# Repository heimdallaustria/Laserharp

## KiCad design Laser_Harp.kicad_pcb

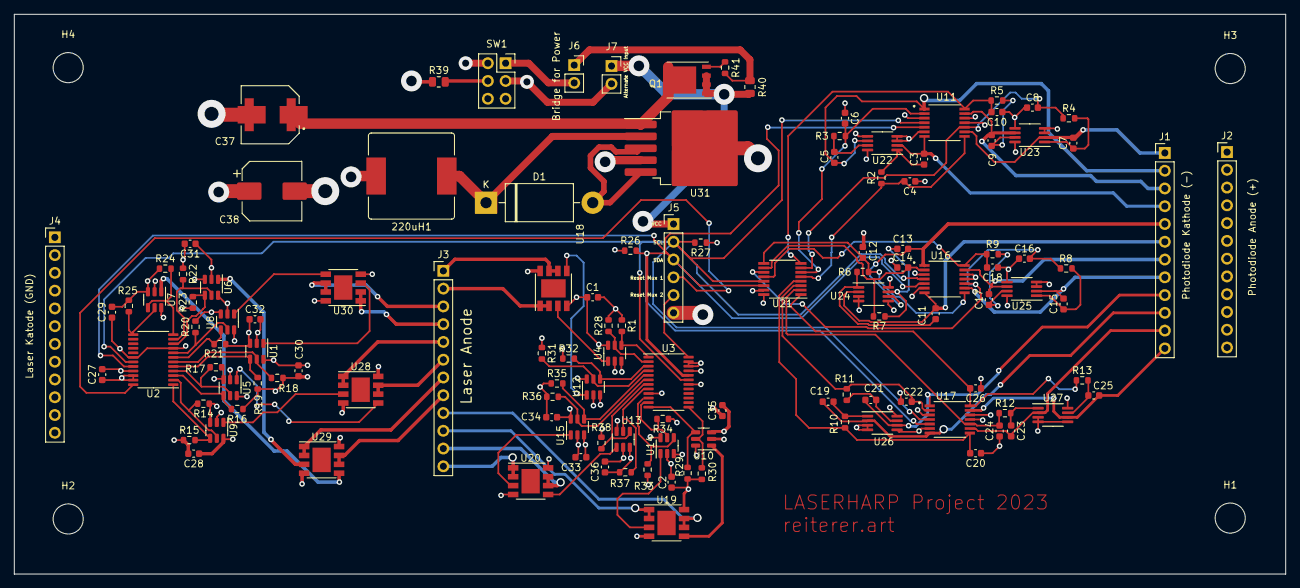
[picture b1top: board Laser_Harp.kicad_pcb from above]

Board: 4 copper layers, 181.7 x 80.0 mm, 125 parts (0 on the bottom side), 97 nets.

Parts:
220uH1: L; L_Bourns_SRR1210A
C1, C2, C27, C28, C29, C30, C31, C32, C33, C34, C35, C36: 0.1uF; C_0603_1608Metric
C3, C5, C7, C9, C11, C13, C15, C17, C19, C21, C23, C25: 22pF; C_0603_1608Metric
C4, C6, C8, C10, C12, C14, C16, C18, C20, C22, C24, C26: 1nF; C_0603_1608Metric
C37: 470uF; CAP_EEEFT1E471AV
C38: 470uF; CP_Elec_8x10
D1: 1N5822; D_DO-201AD_P15.24mm_Horizontal
H1, H2, H3, H4: MountingHole; MountingHole_4.3mm_M4_DIN965
J1, J2, J3, J4: Conn_01x12_Socket; PinHeader_1x12_P2.54mm_Vertical
J5: Conn_01x06_Socket; PinHeader_1x06_P2.54mm_Vertical
J6, J7: Conn_01x02_Pin; PinSocket_1x02_P2.54mm_Vertical
Q1: SQJ147ELP-T1; PowerPAK_SO-8_Single
R1, R14, R15, R16, R17, R18, R19, R20, R21, R22, R23, R24, R25, R26, R27, R28, R29, R30, R31, R33, R34, R35, R36, R37, R38: 10K; R_0603_1608Metric
R2, R3, R4, R5, R6, R7, R8, R9, R10, R11, R12, R13: 100; R_0603_1608Metric
R32: R_Small; R_0603_1608Metric
R39: 130; R_0805_2012Metric
R40: 10K; R_0805_2012Metric
R41: 30; R_0603_1608Metric
SW1: G12JPF; PinSocket_2x03_P2.54mm_Vertical_editpin
U1, U4, U5, U6, U7, U8, U9, U10, U12, U13, U14, U15: MCP4725; SOT-23-6
U2, U3: TCA9548AMRGER; TSSOP-24_4.4x7.8mm_P0.65mm
U11, U16, U17: MCP4432; SOP65P640X120-14N
U18, U19, U20, U28, U29, U30: TS912AIDT; Diodes_SO-8EP
U21: MAX11617; QSOP-16_3.9x4.9mm_P0.635mm
U22, U23, U24, U25, U26, U27: OPA2381AIDGKT; MSOP-8_3x3mm_P0.65mm
U31: LM2576HVS-3.3; TO-263-5_TabPin3

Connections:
3.3V: 220uH1.2, C1.2, C2.2, C27.2, C28.2, C29.2, C30.1, C31.2, C32.1, C33.2, C34.1, C35.2, C36.1, C38.1, R1.1, R14.1, R15.1, R16.1, R17.1, R18.1, R19.1, R20.2, R21.2, R22.1, R23.1, R24.1, R25.2, R26.1, R27.1, R28.1, R29.1, R30.2, R31.1, R32.1, R33.1, R34.1, R35.1, R36.1, R37.2, R38.2, R39.1, U1.3 (VDD), U2.21 (VCC), U3.18 (A2), U3.21 (VCC), U4.3 (VDD), U5.3 (VDD), U6.3 (VDD), U7.3 (VDD), U8.3 (VDD), U9.3 (VDD), U10.3 (VDD), U11.12 (VCC), U12.3 (VDD), U13.3 (VDD), U14.3 (VDD), U15.3 (VDD), U16.11 (A1), U16.12 (VCC), U17.3 (A0), U17.12 (VCC), U18.8 (VCC_2), U19.8 (VCC_2), U20.8 (VCC_2), U21.16 (Vdd), U22.8 (V+), U23.8 (V+), U24.8 (V+), U25.8 (V+), U26.8 (V+), U27.8 (V+), U28.8 (VCC_2), U29.8 (VCC_2), U30.8 (VCC_2), U31.4 (FB)
+12V: J5.1, J7.1, Q1.1 (Source), Q1.2 (Source), Q1.3 (Source), R40.1
ADC_IN0: C4.2, R2.1, U11.8 (P1W), U21.5 (AIN0)
ADC_IN1: C6.2, R3.1, U11.2 (P3B), U21.6 (AIN1)
ADC_IN2: C8.2, R4.1, U11.10 (P0B), U21.7 (AIN2)
ADC_IN3: C10.2, R5.1, U11.14 (P2W), U21.8 (AIN3)
ADC_IN4: C12.2, R6.1, U16.8 (P1W), U21.9 (AIN4)
ADC_IN5: C14.2, R7.1, U16.2 (P3B), U21.10 (AIN5)
ADC_IN6: C16.2, R8.1, U16.10 (P0B), U21.11 (AIN6)
ADC_IN7: C18.2, R9.1, U16.14 (P2W), U21.12 (AIN7)
ADC_IN8: C20.2, R10.1, U17.8 (P1W), U21.4 (AIN8)
ADC_IN9: C22.2, R11.1, U17.2 (P3B), U21.3 (AIN9)
ADC_IN10: C24.2, R12.1, U17.10 (P0B), U21.2 (AIN10)
ADC_IN11: C26.2, R13.1, U17.14 (P2W), U21.1 (AIN11)
GND: C1.1, C2.1, C4.1, C6.1, C8.1, C10.1, C12.1, C14.1, C16.1, C18.1, C20.1, C22.1, C24.1, C26.1, C27.1, C28.1, C29.1, C30.2, C31.1, C32.2, C33.1, C34.2, C35.1, C36.2, C37.2, C38.2, D1.2 (A), J2.1, J2.2, J2.3, J2.4, J2.5, J2.6, J2.7, J2.8, J2.9, J2.10, J2.11, J2.12, J4.1, J4.2, J4.3, J4.4, J4.5, J4.6, J4.7, J4.8, J4.9, J4.10, J4.11, J4.12, J5.6, J7.2, SW1.2, SW1.6, U1.2 (VSS), U1.6 (A0), U2.9 (GND), U2.18 (A2), U2.22 (A0), U2.23 (A1), U3.9 (GND), U3.22 (A0), U3.23 (A1), U4.2 (VSS), U4.6 (A0), U5.2 (VSS), U5.6 (A0), U6.2 (VSS), U6.6 (A0), U7.2 (VSS), U7.6 (A0), U8.2 (VSS), U8.6 (A0), U9.2 (VSS), U9.6 (A0), U10.2 (VSS), U10.6 (A0), U11.3 (A0), U11.6 (GND), U11.11 (A1), U12.2 (VSS), U12.6 (A0), U13.2 (VSS), U13.6 (A0), U14.2 (VSS), U14.6 (A0), U15.2 (VSS), U15.6 (A0), U16.3 (A0), U16.6 (GND), U17.6 (GND), U17.11 (A1), U18.4 (VCC), U19.4 (VCC), U20.4 (VCC), U21.15 (GND), U22.3 (INA+), U22.4 (V-), U22.5 (INB+), U23.3 (INA+), U23.4 (V-), U23.5 (INB+), U24.3 (INA+), U24.4 (V-), U24.5 (INB+), U25.3 (INA+), U25.4 (V-), U25.5 (INB+), U26.3 (INA+), U26.4 (V-), U26.5 (INB+), U27.3 (INA+), U27.4 (V-), U27.5 (INB+), U28.4 (VCC), U29.4 (VCC), U30.4 (VCC), U31.3 (GND), U31.5 (~ON/OFF)
Laser0: J3.2, U18.1 (OUT1), U18.2 (NEG1)
Laser1: J3.1, U18.6 (NEG2), U18.7 (OUT2)
Laser2: J3.12, U20.1 (OUT1), U20.2 (NEG1)
Laser3: J3.11, U20.6 (NEG2), U20.7 (OUT2)
Laser4: J3.10, U19.1 (OUT1), U19.2 (NEG1)
Laser5: J3.9, U19.6 (NEG2), U19.7 (OUT2)
Laser6: J3.5, U28.1 (OUT1), U28.2 (NEG1)
Laser7: J3.6, U28.6 (NEG2), U28.7 (OUT2)
Laser8: J3.4, U30.1 (OUT1), U30.2 (NEG1)
Laser9: J3.3, U30.6 (NEG2), U30.7 (OUT2)
Laser10: J3.7, U29.1 (OUT1), U29.2 (NEG1)
Laser11: J3.8, U29.6 (NEG2), U29.7 (OUT2)
NReset_MUX_1: J5.4, U2.24 (~RESET)
NReset_MUX_2: J5.5, U3.24 (~RESET)
unnamed: 220uH1.1, D1.1 (K), U31.2 (OUT)
unnamed: J6.1, R40.2, R41.2
unnamed: J6.2, SW1.1
unnamed: C37.1, Q1.5 (Drain), U31.1 (VIN)
unnamed: Q1.4 (Gate), R41.1
unnamed: R39.2, SW1.5
unnamed: R18.2, U1.5 (SCL), U2.6 (SC2)
unnamed: R19.2, U1.4 (SDA), U2.5 (SD2)
unnamed: U1.1 (VOUT), U30.3 (POS1)
unnamed: R14.2, U2.2 (SC0), U9.5 (SCL)
unnamed: R17.2, U2.4 (SC1), U5.5 (SCL)
unnamed: R20.1, U2.8 (SC3), U8.5 (SCL)
unnamed: R22.2, U2.11 (SC4), U6.5 (SCL)
unnamed: R25.1, U2.13 (SC5), U7.5 (SCL)
unnamed: R15.2, U2.1 (SD0), U9.4 (SDA)
unnamed: R16.2, U2.3 (SD1), U5.4 (SDA)
unnamed: R21.1, U2.7 (SD3), U8.4 (SDA)
unnamed: R23.2, U2.10 (SD4), U6.4 (SDA)
unnamed: R24.2, U2.12 (SD5), U7.4 (SDA)
unnamed: R28.2, U3.2 (SC0), U4.5 (SCL)
unnamed: R1.2, U3.1 (SD0), U4.4 (SDA)
unnamed: R30.1, U3.13 (SC5), U10.5 (SCL)
unnamed: R29.2, U3.12 (SD5), U10.4 (SDA)
unnamed: U10.1 (VOUT), U19.5 (POS2)
unnamed: R31.2, U3.4 (SC1), U12.5 (SCL)
unnamed: R32.2, U3.3 (SD1), U12.4 (SDA)
unnamed: U12.1 (VOUT), U18.5 (POS2)
unnamed: R37.1, U3.8 (SC3), U13.5 (SCL)
unnamed: R38.1, U3.7 (SD3), U13.4 (SDA)
unnamed: U13.1 (VOUT), U20.5 (POS2)
unnamed: R34.2, U3.11 (SC4), U14.5 (SCL)
unnamed: R33.2, U3.10 (SD4), U14.4 (SDA)
unnamed: U14.1 (VOUT), U19.3 (POS1)
unnamed: R36.2, U3.6 (SC2), U15.5 (SCL)
unnamed: R35.2, U3.5 (SD2), U15.4 (SDA)
unnamed: U15.1 (VOUT), U20.3 (POS1)
unnamed: U4.1 (VOUT), U18.3 (POS1)
unnamed: C3.1, R2.2, U22.1 (OUTA)
unnamed: C5.1, R3.2, U22.7 (OUTB)
unnamed: C7.1, R4.2, U23.1 (OUTA)
unnamed: C9.1, R5.2, U23.7 (OUTB)
unnamed: C11.1, R6.2, U24.1 (OUTA)
unnamed: C13.1, R7.2, U24.7 (OUTB)
unnamed: C15.1, R8.2, U25.1 (OUTA)
unnamed: C17.1, R9.2, U25.7 (OUTB)
unnamed: C19.1, R10.2, U26.1 (OUTA)
unnamed: C21.1, R11.2, U26.7 (OUTB)
unnamed: C23.1, R12.2, U27.1 (OUTA)
unnamed: C25.1, R13.2, U27.7 (OUTB)
unnamed: U9.1 (VOUT), U28.3 (POS1)
unnamed: U5.1 (VOUT), U28.5 (POS2)
unnamed: U6.1 (VOUT), U29.3 (POS1)
unnamed: U7.1 (VOUT), U29.5 (POS2)
unnamed: U8.1 (VOUT), U30.5 (POS2)
PHOTO_0_K: C3.2, J1.4, U11.7 (P1B), U22.2 (INA-)
PHOTO_1_K: C5.2, J1.2, U11.1 (P3W), U22.6 (INB-)
PHOTO_2_K: C7.2, J1.1, U11.9 (P0W), U23.2 (INA-)
PHOTO_3_K: C9.2, J1.3, U11.13 (P2B), U23.6 (INB-)
PHOTO_4_K: C11.2, J1.6, U16.7 (P1B), U24.2 (INA-)
PHOTO_5_K: C13.2, J1.5, U16.1 (P3W), U24.6 (INB-)
PHOTO_6_K: C15.2, J1.8, U16.9 (P0W), U25.2 (INA-)
PHOTO_7_K: C17.2, J1.7, U16.13 (P2B), U25.6 (INB-)
PHOTO_8_K: C19.2, J1.10, U17.7 (P1B), U26.2 (INA-)
PHOTO_9_K: C21.2, J1.9, U17.1 (P3W), U26.6 (INB-)
PHOTO_10_K: C23.2, J1.11, U17.9 (P0W), U27.2 (INA-)
PHOTO_11_K: C25.2, J1.12, U17.13 (P2B), U27.6 (INB-)
SCL: J5.2, R27.2, U2.19 (SCL), U3.19 (SCL), U11.4 (SCL), U16.4 (SCL), U17.4 (SCL), U21.13 (SCL)
SDA: J5.3, R26.2, U2.20 (SDA), U3.20 (SDA), U11.5 (SDA), U16.5 (SDA), U17.5 (SDA), U21.14 (SDA)

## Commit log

2024-02-03 kicad
2024-02-03 Add files via upload
    laserharp control
2024-02-05 Create laser_harp_control
2024-02-05 minor typo fixes
2024-02-28 Rename laser_harp_control to old/laserharp_control
2024-02-28 Rename laserv1.py to python/laserv1.py
2024-02-28 Rename Laser_Harp.kicad_prl to Kicad/Laser_Harp.kicad_prl
2024-02-28 Rename Laser_Harp.kicad_pro to Kicad/Laser_Harp.kicad_pro
2024-02-28 Rename Laser_Harp.pro to Kicad/Laser_Harp.pro
2024-02-28 Rename python/A#1.wav to python/Samples/Harp/A#1.wav
